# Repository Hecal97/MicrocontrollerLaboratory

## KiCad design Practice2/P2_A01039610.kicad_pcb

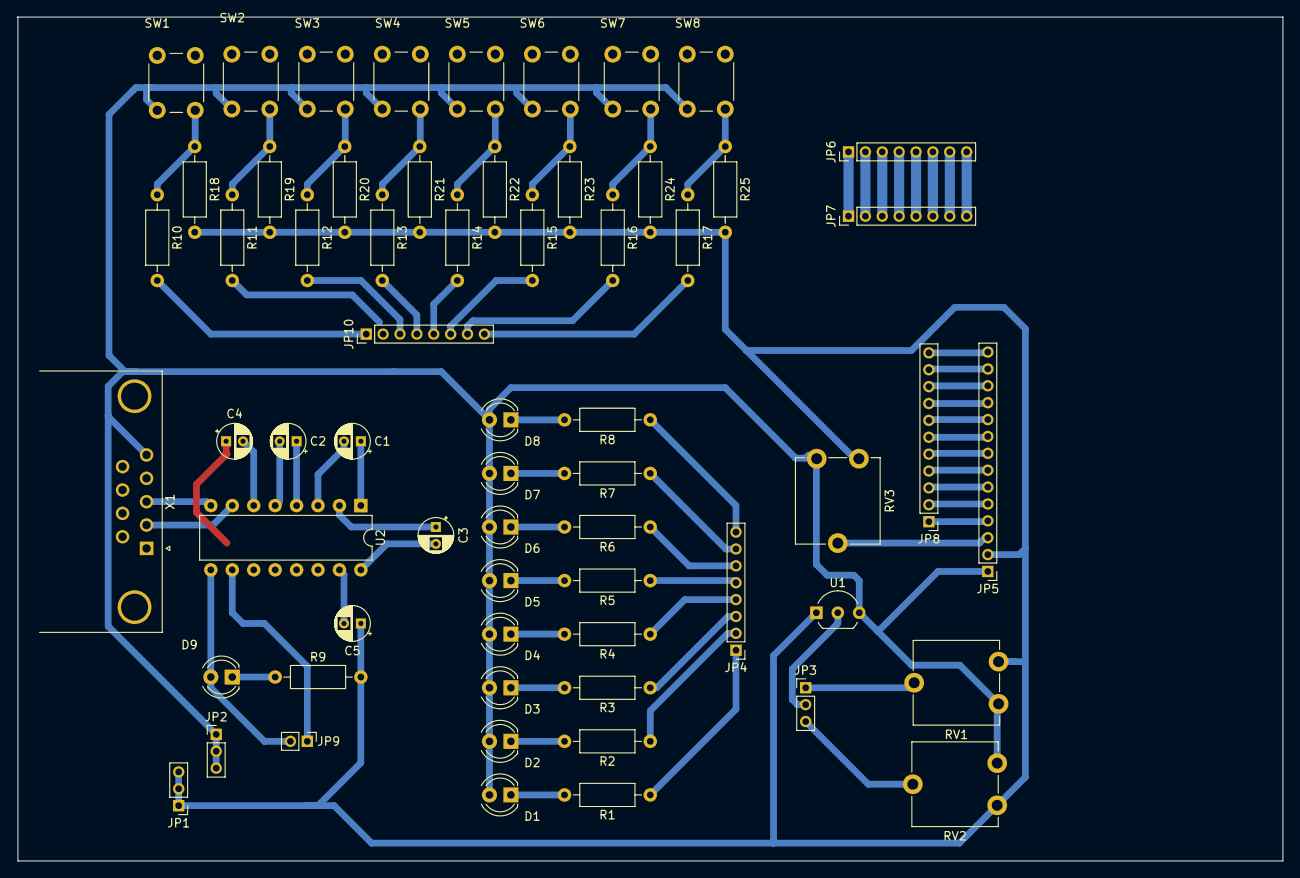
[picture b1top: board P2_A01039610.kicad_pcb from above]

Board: 2 copper layers, 150.0 x 100.0 mm, 63 parts (0 on the bottom side), 69 nets.

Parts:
C1, C2, C3, C4, C5: 10u; CP_Radial_D4.0mm_P2.00mm
D1, D2, D3, D4, D5, D6, D7, D8, D9: LED; LED_D4.0mm
JP1, JP2, JP3: PINHD-1X3; PinHeader_1x03_P2.00mm_Vertical
JP4, JP6, JP7, JP10: PINHD-1X8; PinHeader_1x08_P2.00mm_Vertical
JP5: PINHD-1X14; PinHeader_1x14_P2.00mm_Vertical
JP8: PINHD-1X11; PinHeader_1x11_P2.00mm_Vertical
JP9: PINHD-1X2; PinHeader_1x02_P2.00mm_Vertical
R1, R2, R3, R4, R5, R6, R7, R8, R9: 470; R_Axial_DIN0207_L6.3mm_D2.5mm_P10.16mm_Horizontal
R10, R11, R12, R13, R14, R15, R16, R17: 1K; R_Axial_DIN0207_L6.3mm_D2.5mm_P10.16mm_Horizontal
R18, R19, R20, R21, R22, R23, R24, R25: 4.7K; R_Axial_DIN0207_L6.3mm_D2.5mm_P10.16mm_Horizontal
RV1, RV2, RV3: 10K; Potentiometer_ACP_CA9-V10_Vertical
SW1, SW2, SW3, SW4, SW5, SW6, SW7, SW8: SW_PUSH; SW_PUSH_6mm
U1: MCP9700A; TO-92_Inline_Wide
U2: MAX232; DIP-16_W7.62mm
X1: F09HP; DSUB-9_Female_Horizontal_P2.77x2.84mm_EdgePinOffset9.90mm_H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

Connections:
+5V: C3.2, C5.1, JP1.1, JP1.2, JP1.3, JP5.2, R9.2, R18.2, R19.2, R20.2, R21.2, R22.2, R23.2, R24.2, R25.2, RV1.1, RV2.3, RV3.3, U1.1, U2.16
GND: D1.2, D2.2, D3.2, D4.2, D5.2, D6.2, D7.2, D8.2, JP2.1, JP2.2, JP2.3, JP5.1, RV1.3, RV2.1, RV3.1, SW1.1, SW2.1, SW3.1, SW4.1, SW5.1, SW6.1, SW7.1, SW8.1, U1.3, X1.5
unnamed: C1.1, U2.1
unnamed: C1.2, U2.3
unnamed: C2.1, U2.4
unnamed: C2.2, U2.5
unnamed: C3.1, U2.2
unnamed: C4.1, C5.2, U2.15
unnamed: C4.2, U2.6
unnamed: D1.1, R1.2
unnamed: D2.1, R2.2
unnamed: D3.1, R3.2
unnamed: D4.1, R4.2
unnamed: D5.1, R5.2
unnamed: D6.1, R6.2
unnamed: D7.1, R7.2
unnamed: D8.1, R8.2
unnamed: D9.1, R9.1
unnamed: D9.2, JP9.2, U2.9
unnamed: JP3.1, RV1.2
unnamed: JP3.2, U1.2
unnamed: JP3.3, RV2.2
unnamed: JP4.1, R1.1
unnamed: JP4.2, R2.1
unnamed: JP4.3, R3.1
unnamed: JP4.4, R4.1
unnamed: JP4.5, R5.1
unnamed: JP4.6, R6.1
unnamed: JP4.7, R7.1
unnamed: JP4.8, R8.1
unnamed: JP5.3, RV3.2
unnamed: JP5.4, JP8.1
unnamed: JP5.5, JP8.2
unnamed: JP5.6, JP8.3
unnamed: JP5.7, JP8.4
unnamed: JP5.8, JP8.5
unnamed: JP5.9, JP8.6
unnamed: JP5.10, JP8.7
unnamed: JP5.11, JP8.8
unnamed: JP5.12, JP8.9
unnamed: JP5.13, JP8.10
unnamed: JP5.14, JP8.11
unnamed: JP6.1, JP7.1
unnamed: JP6.2, JP7.2
unnamed: JP6.3, JP7.3
unnamed: JP6.4, JP7.4
unnamed: JP6.5, JP7.5
unnamed: JP6.6, JP7.6
unnamed: JP6.7, JP7.7
unnamed: JP6.8, JP7.8
unnamed: JP9.1, U2.10
unnamed: JP10.1, R10.2
unnamed: JP10.2, R11.2
unnamed: JP10.3, R12.2
unnamed: JP10.4, R13.2
unnamed: JP10.5, R14.2
unnamed: JP10.6, R15.2
unnamed: JP10.7, R16.2
unnamed: JP10.8, R17.2
unnamed: R10.1, R18.1, SW1.2
unnamed: R11.1, R19.1, SW2.2
unnamed: R12.1, R20.1, SW3.2
unnamed: R13.1, R21.1, SW4.2
unnamed: R14.1, R22.1, SW5.2
unnamed: R15.1, R23.1, SW6.2
unnamed: R16.1, R24.1, SW7.2
unnamed: R17.1, R25.1, SW8.2
unnamed: U2.7, X1.2
unnamed: U2.8, X1.3
